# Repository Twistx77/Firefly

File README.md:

# Firefly <h1> 
Open WIFI-enabled RGB lamp with temperature, humidity, suspended air particles and eCO2 sensors.

# List of components <h2> 

| Quantity | Component             | Image                                                        |
| -------- | --------------------- | ------------------------------------------------------------ |
| 1        | ESP8266 Wemos D1 Mini |  |
| 10       | WS2812B               |  |
|12 		| Capacitor 0603 0.1uF ||
|2			| Resistor 0603 ||
|1			| APDS-9960	Breakout Board||
|(Optional)* 1 	| DHT11 ||
|(Optional)* 1   | CCS811 + HDC1080 Breakout Board ||

*Even though both components can be soldered to the same board or none of them, it is recommended to chose the CCS811 + HDC1080 module if you can pay it since it not only provides more information (TVOC 's and eCO2) but the temperature and humidity measurements are more accurate.

You can get all this components in different websites and I have found that Aliexpress is the cheapest one for most of these modules.

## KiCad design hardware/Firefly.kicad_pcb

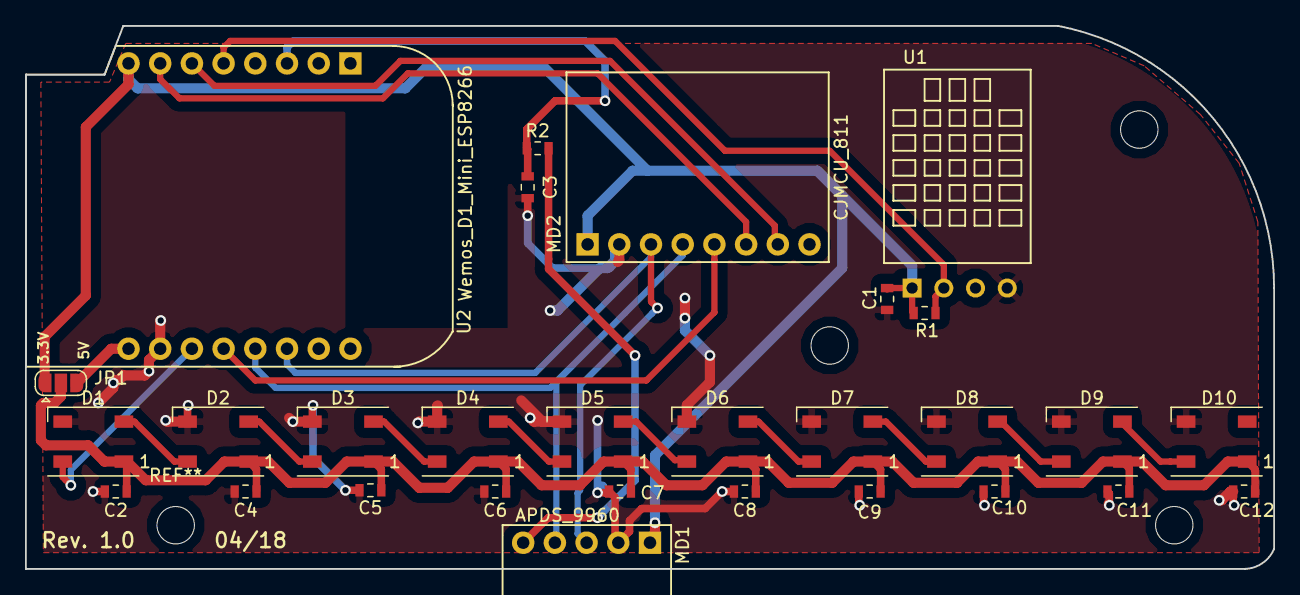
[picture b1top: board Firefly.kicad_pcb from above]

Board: 2 copper layers, 100.0 x 43.5 mm, 29 parts (0 on the bottom side), 22 nets.

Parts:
C1, C2, C3, C4, C5, C6, C7, C8, C9, C10, C11, C12: 0.1uF; C_0603_1608Metric
D1, D2, D3, D4, D5, D6, D7, D8, D9, D10: WS2812B; LED_WS2812B_PLCC4_5.0x5.0mm_P3.2mm
JP1: SolderJumper_3_Open; SolderJumper-3_P1.3mm_Open_RoundedPad1.0x1.5mm
MD1: APDS-9960; MODULE_APDS_9960
MD2: CJMCU-811; MODULE_CJMCU_811
R1, R2: 1K; R_0603_1608Metric
U1: DHT11
U2: ESP8266_D1; Wemos_D1_Mini_ESP8266

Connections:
+3V3: C1.1, JP1.1, MD1.1, MD2.1, R1.1, U1.1, U2.8
+5V: JP1.3, U2.9
/D4: D1.4, U2.11
/D6: R1.2, U1.2, U2.5
/SCL: MD1.3, MD2.3, U2.14
/SDA: MD1.4, MD2.4, U2.13
GND: C1.2, C2.2, C3.2, C4.2, C5.2, C6.2, C7.2, C8.2, C9.2, C10.2, C11.2, C12.2, D1.3, D2.3, D3.3, D4.3, D5.3, D6.3, D7.3, D8.3, D9.3, D10.3, MD1.2, MD2.2, U1.4, U2.10
unnamed: C3.1, R2.2, U2.3
unnamed: C2.1, C4.1, C5.1, C6.1, C7.1, C8.1, C9.1, C10.1, C11.1, C12.1, D1.1, D2.1, D3.1, D4.1, D5.1, D6.1, D7.1, D8.1, D9.1, D10.1, JP1.2
unnamed: D1.2, D2.4
unnamed: D2.2, D3.4
unnamed: D3.2, D4.4
unnamed: D4.2, D5.4
unnamed: D5.2, D6.4
unnamed: D6.2, D7.4
unnamed: D7.2, D8.4
unnamed: D8.2, D9.4
unnamed: D9.2, D10.4
unnamed: MD1.5, R2.1
unnamed: MD2.5, U2.12
unnamed: MD2.6, U2.7
unnamed: MD2.7, U2.6

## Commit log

2018-06-04 Added .gitignore
2018-06-25 Implemented basic gesture functionality and added gerbers to hardware
2018-06-25 Fixed space in Gerbers folder name
2018-06-27 Added components lists
